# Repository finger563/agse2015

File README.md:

View this project on [CADLAB.io](https://cadlab.io/node/972). 

agse2015
========

This repository contains the design and implementation for the AGSE subsystem for the VAC 2015 year.

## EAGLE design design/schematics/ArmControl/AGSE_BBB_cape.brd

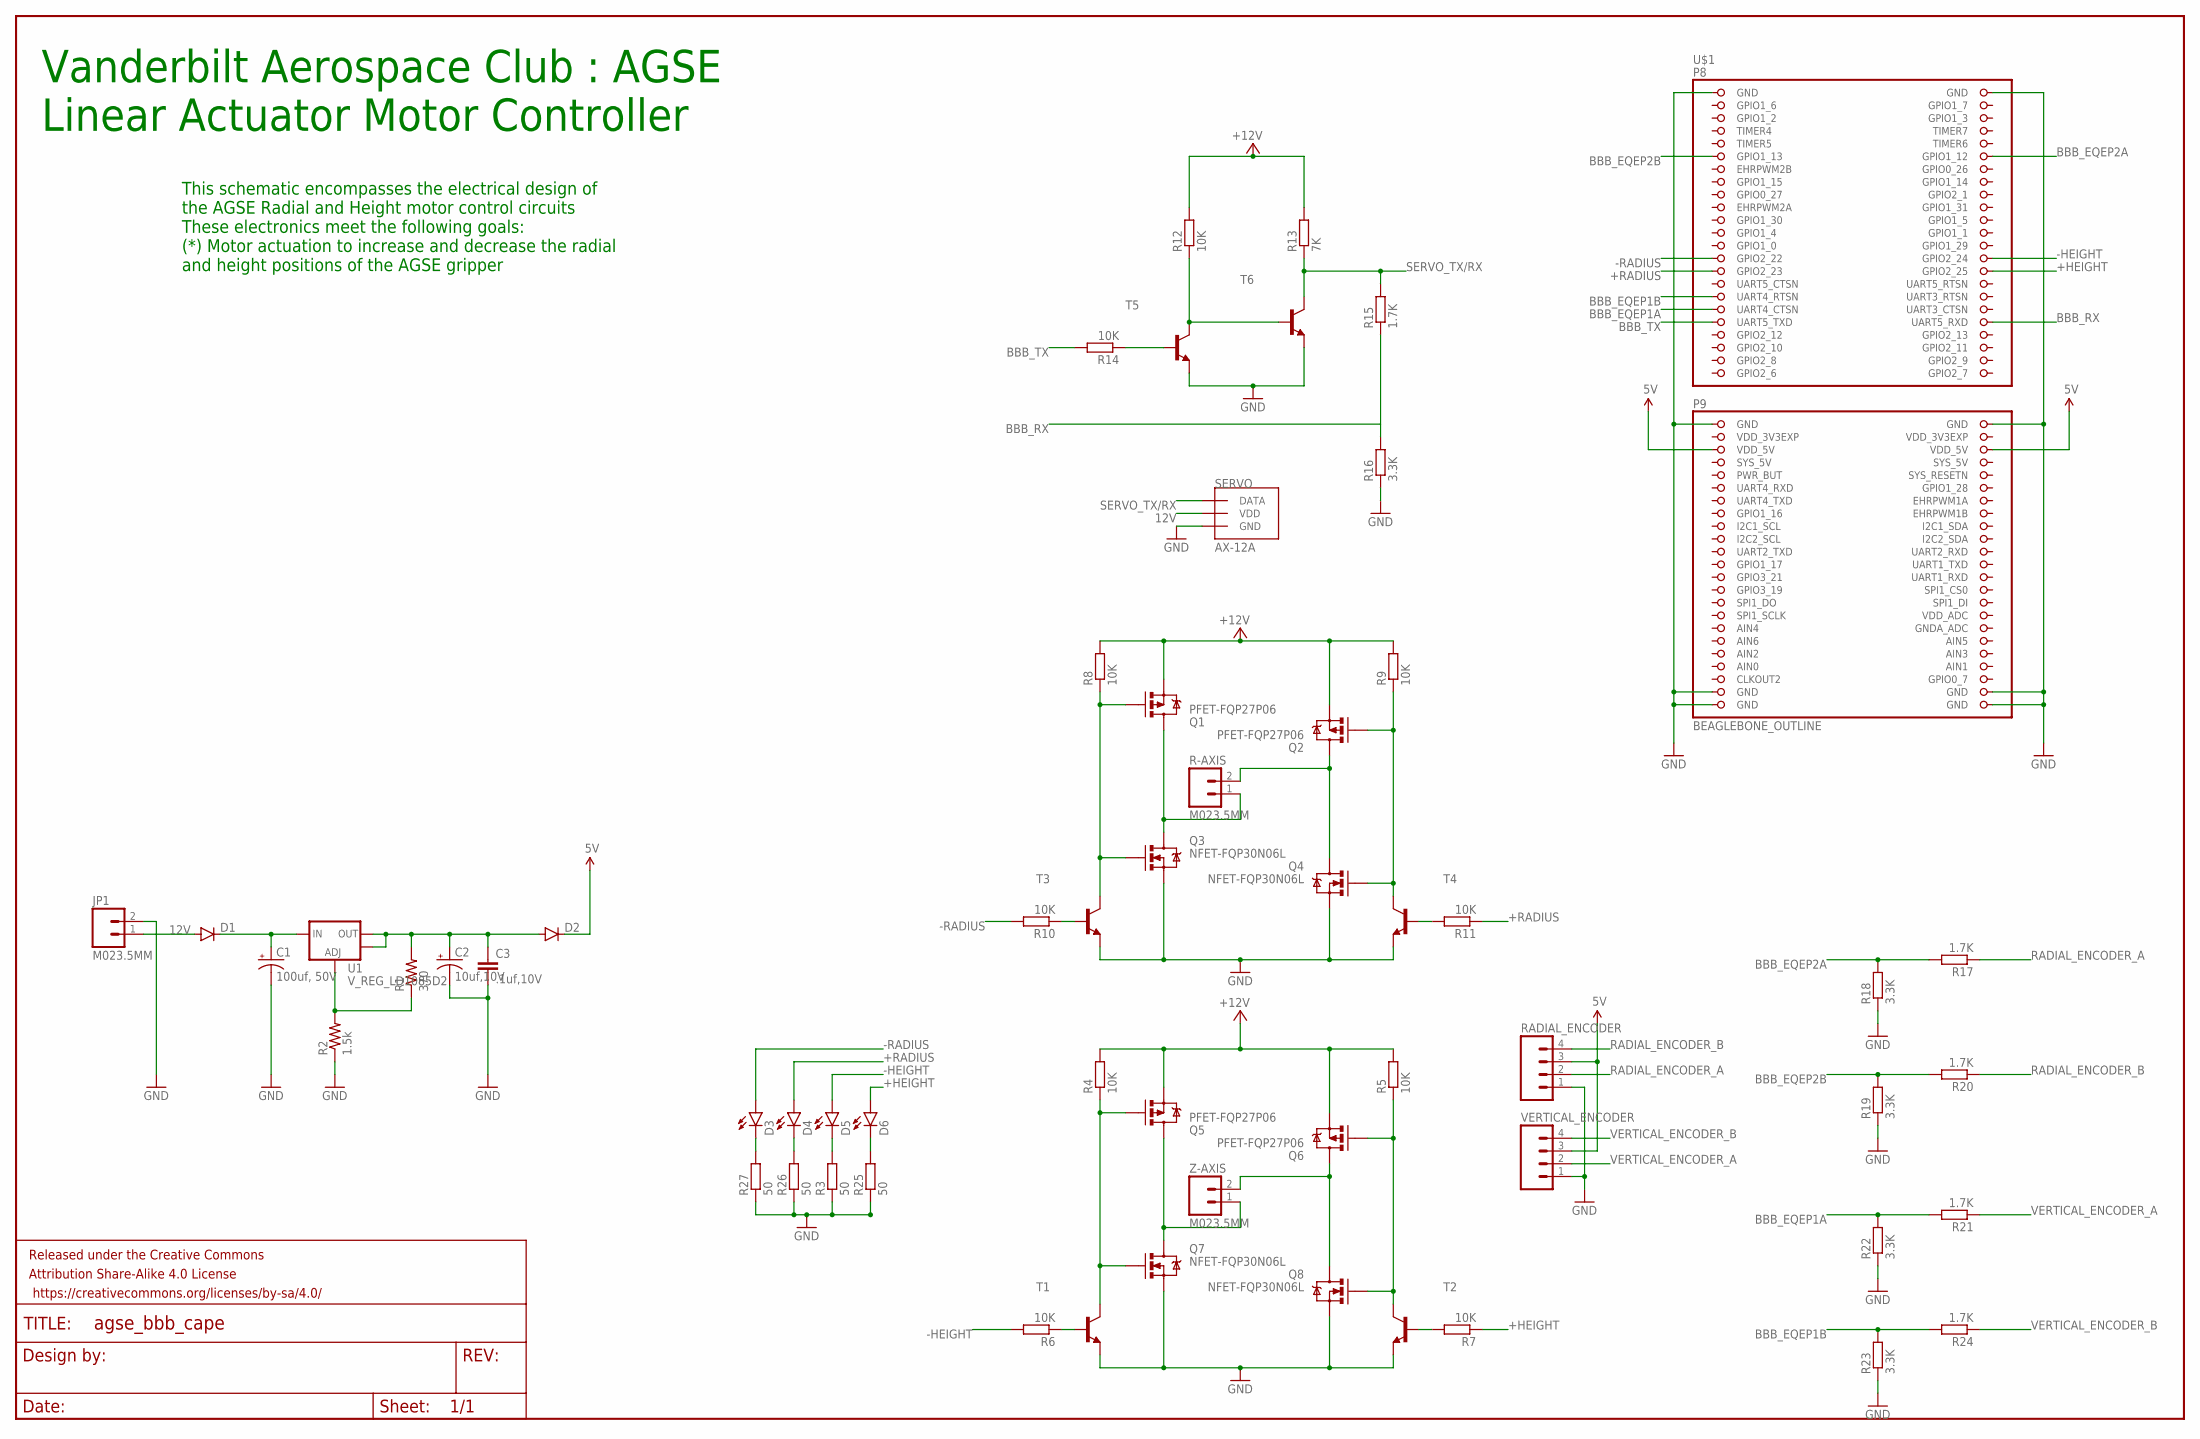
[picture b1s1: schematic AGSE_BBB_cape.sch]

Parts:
C1: 100uf, 50V; PANASONIC_D
C2: 10uf,10V; EIA3216
C3: .1uf,10V; 0402-CAP
D1: DIODESMA; SMA-DIODE
D2: DIODE1N4148; DIODE-1N4148
D3, D4, D5, D6: LED-FKIT-1206; FKIT-LED-1206
FRAME1: FRAME-LEDGER; CREATIVE_COMMONS
JP1: M023.5MM; SCREWTERMINAL-3.5MM-2
Q1, Q2, Q5, Q6: PFET-FQP27P06; TO220V
Q3, Q4, Q7, Q8: NFET-FQP30N06L; TO220V
R1: 370; 0402-RES
R2: 1.5k; 0402-RES
R3, R25, R26, R27: 50; M0805
R4, R5, R6, R7, R8, R9, R10, R11, R12, R14: 10K; M0805
R13: 7K; M0805
R15, R17, R20, R21, R24: 1.7K; M0805
R16, R18, R19, R22, R23: 3.3K; M0805
R-AXIS: M023.5MM; SCREWTERMINAL-3.5MM-2
RADIAL_ENCODER: M04POLAR; MOLEX-1X4
SERVO: AX-12A; SPOX-3
T1, T2, T3, T4, T5, T6: BF820-NPN-SOT23-BEC; SOT23-BEC
U1: V_REG_LD1085D2; D2PACK/A
U$1: BEAGLEBONE_OUTLINE; BEAGLEBONE_SHIELD
VERTICAL_ENCODER: M04POLAR; MOLEX-1X4
Z-AXIS: M023.5MM; SCREWTERMINAL-3.5MM-2

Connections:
5V: D2.C, RADIAL_ENCODER.3, U$1.51 (VDD_5V), U$1.52 (VDD_5V), VERTICAL_ENCODER.3
12V: D1.A, JP1.1, Q1.3 (S), Q2.3 (S), Q5.3 (S), Q6.3 (S), R4.2, R5.2, R8.2, R9.2, R12.2, R13.2, SERVO.P$2 (VDD)
+HEIGHT: D6.A, R7.1, U$1.30 (GPIO2_25)
+RADIUS: D4.A, R11.1, U$1.29 (GPIO2_23)
-HEIGHT: D5.A, R6.2, U$1.28 (GPIO2_24)
-RADIUS: D3.A, R10.2, U$1.27 (GPIO2_22)
AIN0: U$1.85 (AIN0)
BBB_EQEP1A: R21.2, R22.2, U$1.35 (UART4_CTSN)
BBB_EQEP1B: R23.2, R24.2, U$1.33 (UART4_RTSN)
BBB_EQEP2A: R17.2, R18.2, U$1.12 (GPIO1_12)
BBB_EQEP2B: R19.2, R20.2, U$1.11 (GPIO1_13)
BBB_RX: R15.1, R16.2, U$1.38 (UART5_RXD)
BBB_TX: R14.2, U$1.37 (UART5_TXD)
GND: C1.-, C2.C (-), C3.2, JP1.2, Q3.3 (S), Q4.3 (S), Q7.3 (S), Q8.3 (S), R2.1, R3.1, R16.1, R18.1, R19.1, R22.1, R23.1, R25.1, R26.1, R27.1, RADIAL_ENCODER.1, SERVO.P$3 (GND), T1.E, T2.E, T3.E, T4.E, T5.E, T6.E, U$1.1 (GND), U$1.2 (GND), U$1.47 (GND), U$1.48 (GND), U$1.89 (GND), U$1.90 (GND), U$1.91 (GND), U$1.92 (GND), VERTICAL_ENCODER.1
unnamed: D3.C, R27.2
unnamed: D4.C, R26.2
unnamed: C1.+, D1.C, U1.3 (IN)
unnamed: R1.1, R2.2, U1.1 (ADJ)
unnamed: D5.C, R3.2
unnamed: D6.C, R25.2
unnamed: Q5.1 (G), Q7.1 (G), R4.1, T1.C
unnamed: Q6.1 (G), Q8.1 (G), R5.1, T2.C
unnamed: R6.1, T1.B
unnamed: R7.2, T2.B
unnamed: Q1.1 (G), Q3.1 (G), R8.1, T3.C
unnamed: Q2.1 (G), Q4.1 (G), R9.1, T4.C
unnamed: R10.1, T3.B
unnamed: R11.2, T4.B
unnamed: R14.1, T5.B
unnamed: R12.1, T5.C, T6.B
R+: Q1.2 (D), Q3.2 (D), R-AXIS.1
R-: Q2.2 (D), Q4.2 (D), R-AXIS.2
RADIAL_ENCODER_A: R17.1, RADIAL_ENCODER.2
RADIAL_ENCODER_B: R20.1, RADIAL_ENCODER.4
SERVO_TX/RX: R13.1, R15.2, SERVO.P$1 (DATA), T6.C
SYS_5V: U$1.53 (SYS_5V)
VDD_3V3EXP: U$1.49 (VDD_3V3EXP), U$1.50 (VDD_3V3EXP)
VERTICAL_ENCODER_A: R21.1, VERTICAL_ENCODER.2
VERTICAL_ENCODER_B: R24.1, VERTICAL_ENCODER.4
VOUT: C2.A (+), C3.1, D2.A, R1.2, U1.2 (OUT), U1.TAB (OUT)
Z+: Q5.2 (D), Q7.2 (D), Z-AXIS.1
Z-: Q6.2 (D), Q8.2 (D), Z-AXIS.2

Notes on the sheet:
Vanderbilt Aerospace Club : AGSE Linear Actuator Motor Controller
This schematic encompasses the electrical design of the AGSE Radial and Height motor control circuits These electronics meet the following goals: (*) Motor actuation to increase and decrease the radial and height positions of the AGSE gripper

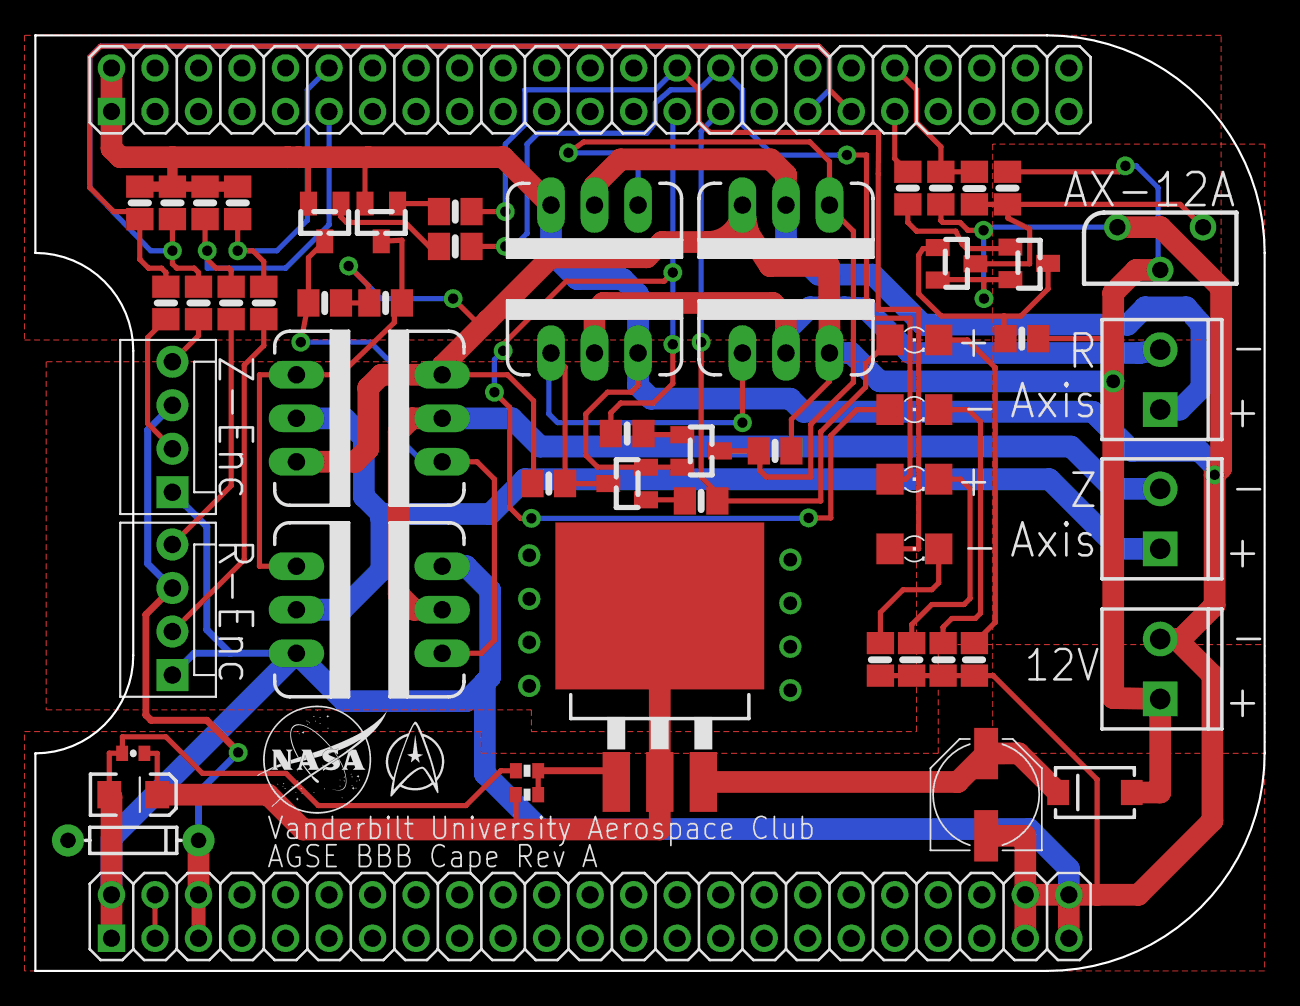
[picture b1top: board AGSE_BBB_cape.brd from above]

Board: 2 copper layers, 71.8 x 54.6 mm, 60 parts (0 on the bottom side), 40 nets.

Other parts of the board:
DRILEGEND: DRILEGEND

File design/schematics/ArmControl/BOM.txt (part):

Partlist exported from C:/Users/Pranav/Downloads/agse2015/design/schematics/ArmControl/AGSE_BBB_cape.sch at 2/26/2015 3:21:17 PM

Part             Value              Device                   Package               Description                                               MANEX        PROD_ID    
C1               100uf, 50V         CAP_POLD                 PANASONIC_D           Capacitor Polarized                                       123-0004264             
C2               10uf,10V           CAP_POL1206              EIA3216               Capacitor Polarized                                       123-0001192             
C3               .1uf,10V           CAP0402-CAP              0402-CAP              Capacitor                                                 123-0001047             
D1                                  DIODESMA                 SMA-DIODE             Diode                                                     130-0001388             
D2                                  DIODE1N4148              DIODE-1N4148          Diode                                                     130-0002546             
D3                                  LED-FKIT-1206            FKIT-LED-1206         LEDs                                                                              
D4                                  LED-FKIT-1206            FKIT-LED-1206         LEDs                                                                              
D5                                  LED-FKIT-1206            FKIT-LED-1206         LEDs                                                                              
D6                                  LED-FKIT-1206            FKIT-LED-1206         LEDs                                                                              
FRAME1           FRAME-LEDGER       FRAME-LEDGER             CREATIVE_COMMONS      Schematic Frame                                                                   
JP1              M023.5MM           M023.5MM                 SCREWTERMINAL-3.5MM-2 Standard 2-pin 0.1" header. Use with                      257-0004040  CONN-08399 
Q1               PFET-FQP27P06      MOSFET-PCHANNELFQP27P06  TO220V                Generic PMOSFET                                                                   
Q2               PFET-FQP27P06      MOSFET-PCHANNELFQP27P06  TO220V                Generic PMOSFET                                                                   
Q3               NFET-FQP30N06L     MOSFET-NCHANNELFQP30N06L TO220V                Common NMOSFET Parts                                                   TRANS-10060
Q4               NFET-FQP30N06L     MOSFET-NCHANNELFQP30N06L TO220V                Common NMOSFET Parts                                                   TRANS-10060
Q5               PFET-FQP27P06      MOSFET-PCHANNELFQP27P06  TO220V                Generic PMOSFET                                                                   
Q6               PFET-FQP27P06      MOSFET-PCHANNELFQP27P06  TO220V                Generic PMOSFET                                                                   
Q7               NFET-FQP30N06L     MOSFET-NCHANNELFQP30N06L TO220V                Common NMOSFET Parts                                                   TRANS-10060
Q8               NFET-FQP30N06L     MOSFET-NCHANNELFQP30N06L TO220V                Common NMOSFET Parts                                                   TRANS-10060
R-AXIS           M023.5MM           M023.5MM                 SCREWTERMINAL-3.5MM-2 Standard 2-pin 0.1" header. Use with                      257-0004040  CONN-08399 
R1               370                RESISTOR0402-RES         0402-RES              Resistor                                                  110-0003316             
R2               1.5k               RESISTOR0402-RES         0402-RES              Resistor                                                  110-0001936             
R3               50                 R-EU_M0805               M0805                 RESISTOR, European symbol                                                         
R4               10K                R-EU_M0805               M0805                 RESISTOR, European symbol                                                         
R5               10K                R-EU_M0805               M0805                 RESISTOR, European symbol                                                         
R6               10K                R-EU_M0805               M0805                 RESISTOR, European symbol                                                         
R7               10K                R-EU_M0805               M0805                 RESISTOR, European symbol                                                         
R8               10K                R-EU_M0805               M0805                 RESISTOR, European symbol                                                         
R9               10K                R-EU_M0805               M0805                 RESISTOR, European symbol                                                         
R10              10K                R-EU_M0805               M0805                 RESISTOR, European symbol                                                         
R11              10K                R-EU_M0805               M0805                 RESISTOR, European symbol                                                         
R12              10K                R-EU_M0805               M0805                 RESISTOR, European symbol                                                         
R13              7K                 R-EU_M0805               M0805                 RESISTOR, European symbol                                                         
R14              10K                R-EU_M0805               M0805                 RESISTOR, European symbol                                                         
R15              1.7K               R-EU_M0805               M0805                 RESISTOR, European symbol                                                         
R16              3.3K               R-EU_M0805               M0805                 RESISTOR, European symbol                                                         
R17              1.7K               R-EU_M0805               M0805                 RESISTOR, European symbol                                                         
R18              3.3K               R-EU_M0805               M0805                 RESISTOR, European symbol                                                         
R19              3.3K               R-EU_M0805               M0805                 RESISTOR, European symbol                                                         
R20              1.7K               R-EU_M0805               M0805                 RESISTOR, European symbol                                                         
R21              1.7K               R-EU_M0805               M0805                 RESISTOR, European symbol                                                         
R22              3.3K               R-EU_M0805               M0805                 RESISTOR, European symbol                                                         
R23              3.3K               R-EU_M0805               M0805                 RESISTOR, European symbol                                                         
R24              1.7K               R-EU_M0805               M0805                 RESISTOR, European symbol                                                         
R25              50                 R-EU_M0805               M0805                 RESISTOR, European symbol                                                         
R26              50                 R-EU_M0805               M0805                 RESISTOR, European symbol                                                         
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
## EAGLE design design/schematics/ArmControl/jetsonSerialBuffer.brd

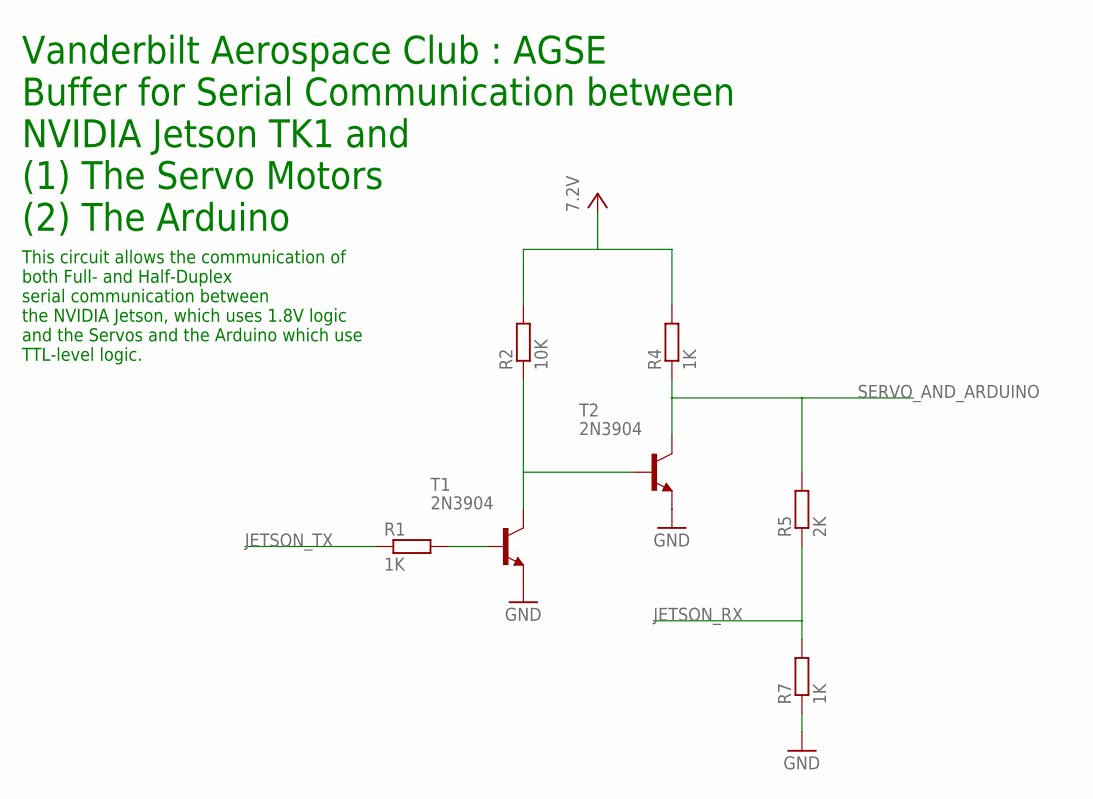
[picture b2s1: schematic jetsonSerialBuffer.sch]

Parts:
R1, R4, R7: 1K; 0309/10
R2: 10K; 0309/10
R5: 2K; 0309/10
T1, T2: 2N3904; TO92

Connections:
GND: R7.1, T1.3 (E), T2.3 (E)
JETSON_RX: R5.1, R7.2
JETSON_TX: R1.1
unnamed: R1.2, T1.2 (B)
unnamed: R2.1, T1.1 (C), T2.2 (B)
SERVO_AND_ARDUINO: R4.1, R5.2, T2.1 (C)
VCC: R2.2, R4.2

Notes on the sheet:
Vanderbilt Aerospace Club : AGSE Buffer for Serial Communication between NVIDIA Jetson TK1 and (1) The Servo Motors (2) The Arduino
This circuit allows the communication of both Full- and Half-Duplex serial communication between the NVIDIA Jetson, which uses 1.8V logic and the Servos and the Arduino which use TTL-level logic.

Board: 2 copper layers, 7 parts (0 on the bottom side), 6 nets, no tracks yet.

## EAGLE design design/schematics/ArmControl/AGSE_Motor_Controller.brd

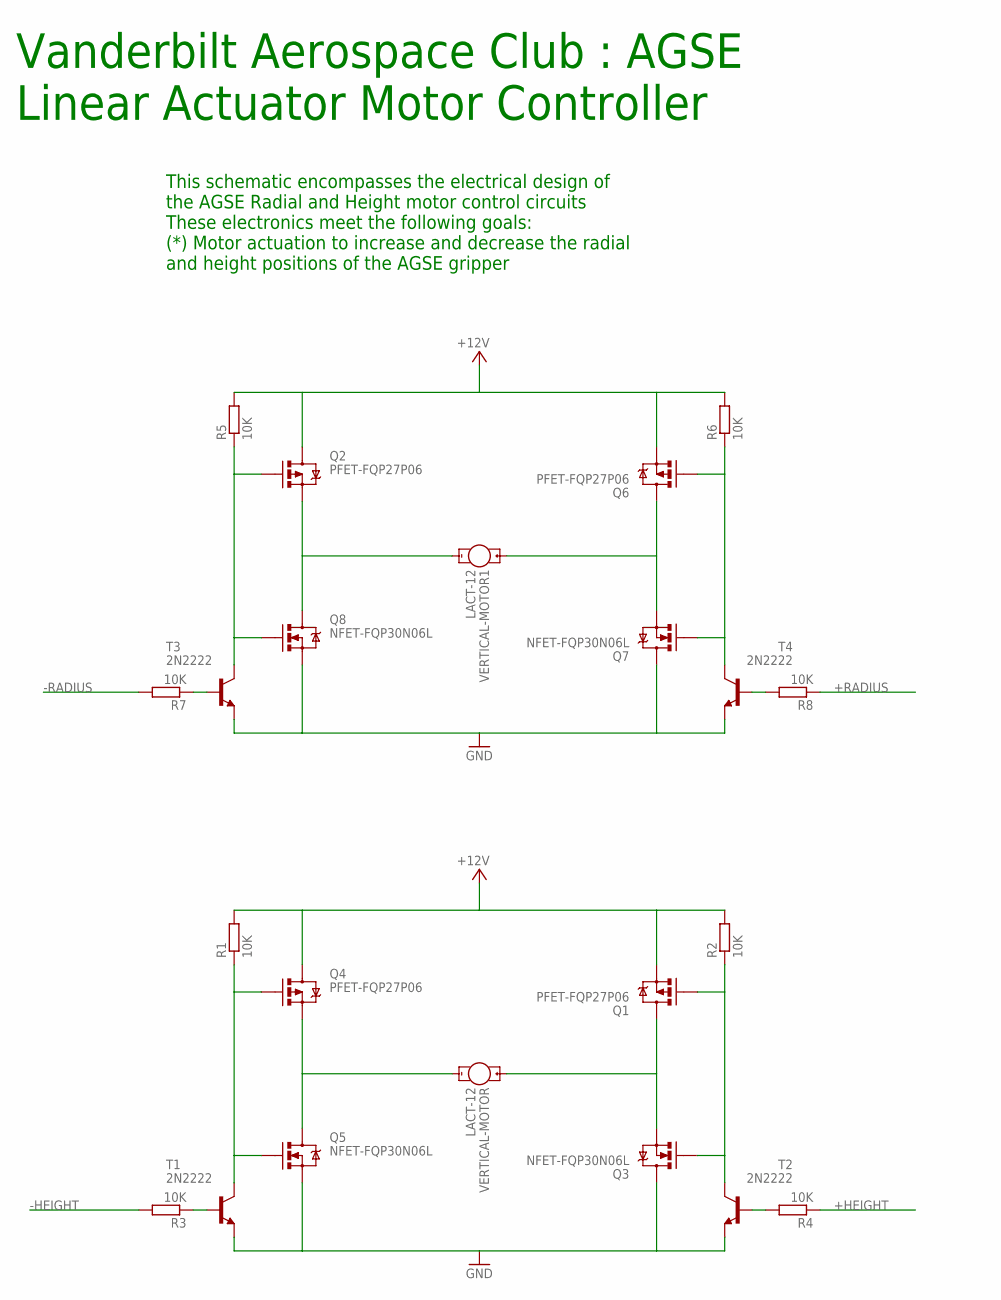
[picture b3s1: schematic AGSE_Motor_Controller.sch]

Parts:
Q1, Q2, Q4, Q6: PFET-FQP27P06; TO220V
Q3, Q5, Q7, Q8: NFET-FQP30N06L; TO220V
R1, R2, R3, R4, R5, R6, R7, R8: 10K; 0207/12
T1, T2, T3, T4: 2N2222; TO18
VERTICAL-MOTOR, VERTICAL-MOTOR1: LACT-12; VIBE-MOTOR-10MM

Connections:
+5V: Q1.3 (S), Q2.2 (D), Q4.2 (D), Q6.3 (S), R1.2, R2.2, R5.2, R6.2
+HEIGHT: R4.1
+RADIUS: R8.1
-HEIGHT: R3.2
-RADIUS: R7.2
GND: Q3.2 (D), Q5.3 (S), Q7.2 (D), Q8.3 (S), T1.1 (E), T2.1 (E), T3.1 (E), T4.1 (E)
unnamed: Q4.3 (S), Q5.2 (D), VERTICAL-MOTOR.-
unnamed: Q1.2 (D), Q3.3 (S), VERTICAL-MOTOR.+
unnamed: Q4.1 (G), Q5.1 (G), R1.1, T1.3 (C)
unnamed: Q1.1 (G), Q3.1 (G), R2.1, T2.3 (C)
unnamed: R3.1, T1.2 (B)
unnamed: R4.2, T2.2 (B)
unnamed: Q6.2 (D), Q7.3 (S), VERTICAL-MOTOR1.+
unnamed: Q2.3 (S), Q8.2 (D), VERTICAL-MOTOR1.-
unnamed: Q2.1 (G), Q8.1 (G), R5.1, T3.3 (C)
unnamed: Q6.1 (G), Q7.1 (G), R6.1, T4.3 (C)
unnamed: R7.1, T3.2 (B)
unnamed: R8.2, T4.2 (B)

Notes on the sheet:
Vanderbilt Aerospace Club : AGSE Linear Actuator Motor Controller
This schematic encompasses the electrical design of the AGSE Radial and Height motor control circuits These electronics meet the following goals: (*) Motor actuation to increase and decrease the radial and height positions of the AGSE gripper

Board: 2 copper layers, 22 parts (0 on the bottom side), 14 nets, no tracks yet.

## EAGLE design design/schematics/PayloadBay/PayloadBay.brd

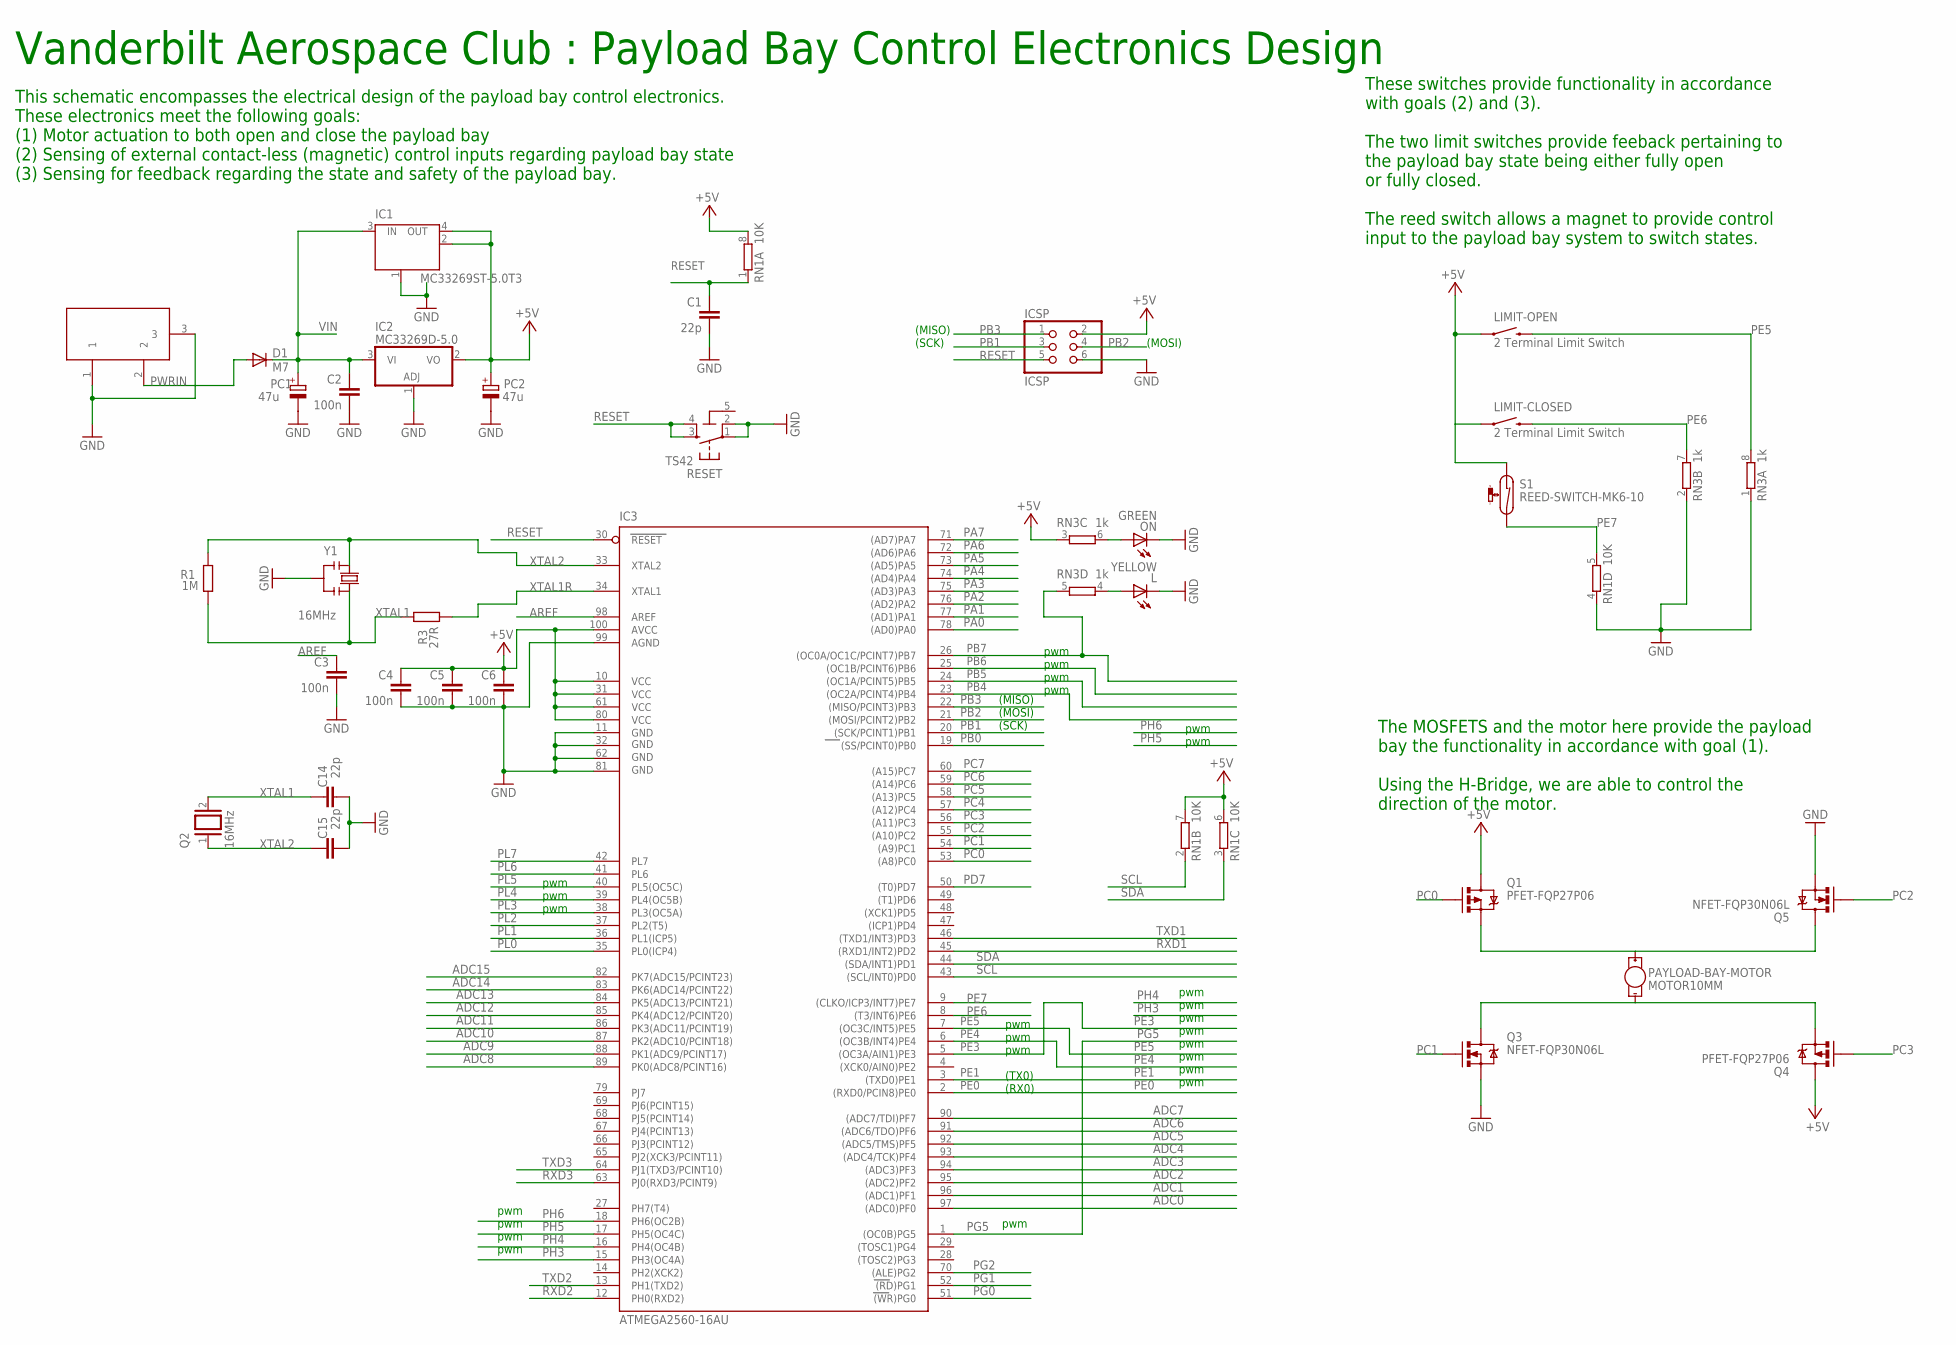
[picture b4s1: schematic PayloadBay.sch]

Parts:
C1, C14, C15: 22p; C0603-ROUND
C2, C3, C4, C5, C6: 100n; C0603-ROUND
D1: M7; SMB
IC1: MC33269ST-5.0T3; SOT223
IC2: MC33269D-5.0; DPACK
IC3: ATMEGA2560-16AU; TQFP100
ICSP: ICSP; 2X03
L: YELLOW; CHIP-LED0805
LIMIT-CLOSED: 2 Terminal Limit Switch; TACTILE-PTH-12MM
LIMIT-OPEN: 2 Terminal Limit Switch; TACTILE-PTH-12MM
ON: GREEN; CHIP-LED0805
PAYLOAD-BAY-MOTOR: MOTOR10MM; VIBE-MOTOR-10MM
PC1, PC2: 47u; PANASONIC_D
Q1, Q4: PFET-FQP27P06; TO220V
Q2: 16MHz; QS
Q3, Q5: NFET-FQP30N06L; TO220V
R1: 1M; R0603-ROUND
R3: 27R; R0603-ROUND
RESET: TS42
RN1: 10K; CAT16
RN3: 1k; CAY16
S1: REED-SWITCH-MK6-10; MK6-10
X1: DC21MMX; DC-21MM
Y1: 16MHz; RESONATOR

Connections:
5-GND: RESET.5 (5-GND)
+5V: C4.1, C5.1, C6.1, IC1.2 (OUT), IC1.4 (OUT), IC2.2 (VO), IC3.10 (VCC), IC3.31 (VCC1), IC3.61 (VCC2), IC3.80 (VCC3), IC3.100 (AVCC), ICSP.2, LIMIT-CLOSED.1, LIMIT-OPEN.1, PC2.+, Q1.2 (D), Q4.2 (D), RN1.6 (2), RN1.7 (2), RN1.8 (2), RN3.3 (1), S1.1
ADC0: IC3.97 ((ADC0)PF0)
ADC1: IC3.96 ((ADC1)PF1)
ADC2: IC3.95 ((ADC2)PF2)
ADC3: IC3.94 ((ADC3)PF3)
ADC4: IC3.93 ((ADC4/TCK)PF4)
ADC5: IC3.92 ((ADC5/TMS)PF5)
ADC6: IC3.91 ((ADC6/TDO)PF6)
ADC7: IC3.90 ((ADC7/TDI)PF7)
ADC8: IC3.89 (PK0(ADC8/PCINT16))
ADC9: IC3.88 (PK1(ADC9/PCINT17))
ADC10: IC3.87 (PK2(ADC10/PCINT18))
ADC11: IC3.86 (PK3(ADC11/PCINT19))
ADC12: IC3.85 (PK4(ADC12/PCINT20))
ADC13: IC3.84 (PK5(ADC13/PCINT21))
ADC14: IC3.83 (PK6(ADC14/PCINT22))
ADC15: IC3.82 (PK7(ADC15/PCINT23))
AREF: C3.1, IC3.98 (AREF)
GND: C1.2, C2.2, C3.2, C4.2, C5.2, C6.2, C14.1, C15.1, IC1.1 (GND/ADJ), IC2.1 (ADJ), IC3.11 (GND), IC3.32 (GND1), IC3.62 (GND2), IC3.81 (GND3), IC3.99 (AGND), ICSP.6, L.C, ON.C, PC1.-, PC2.-, Q3.3 (S), Q5.3 (S), RESET.1, RESET.2, RN1.4 (1), RN3.1, RN3.2 (1), X1.1, X1.3, Y1.2
unnamed: PAYLOAD-BAY-MOTOR.+, Q1.3 (S), Q5.2 (D)
unnamed: L.A, RN3.4 (1)
unnamed: ON.A, RN3.6 (2)
unnamed: PAYLOAD-BAY-MOTOR.-, Q3.2 (D), Q4.3 (S)
PA0: IC3.78 ((AD0)PA0)
PA1: IC3.77 ((AD1)PA1)
PA2: IC3.76 ((AD2)PA2)
PA3: IC3.75 ((AD3)PA3)
PA4: IC3.74 ((AD4)PA4)
PA5: IC3.73 ((AD5)PA5)
PA6: IC3.72 ((AD6)PA6)
PA7: IC3.71 ((AD7)PA7)
PB0: IC3.19 ((SS/PCINT0)PB0)
PB1: IC3.20 ((SCK/PCINT1)PB1), ICSP.3
PB2: IC3.21 ((MOSI/PCINT2)PB2), ICSP.4
PB3: IC3.22 ((MISO/PCINT3)PB3), ICSP.1
PB4: IC3.23 ((OC2A/PCINT4)PB4)
PB5: IC3.24 ((OC1A/PCINT5)PB5)
PB6: IC3.25 ((OC1B/PCINT6)PB6)
PB7: IC3.26 ((OC0A/OC1C/PCINT7)PB7), RN3.5 (2)
PC0: IC3.53 ((A8)PC0)
PC1: IC3.54 ((A9)PC1), Q3.1 (G)
PC2: IC3.55 ((A10)PC2), Q5.1 (G)
PC3: IC3.56 ((A11)PC3), Q4.1 (G)
PC4: IC3.57 ((A12)PC4)
PC5: IC3.58 ((A13)PC5)
PC6: IC3.59 ((A14)PC6)
PC7: IC3.60 ((A15)PC7)
PD7: IC3.50 ((T0)PD7)
PE0: IC3.2 ((RXD0/PCIN8)PE0)
PE1: IC3.3 ((TXD0)PE1)
PE3: IC3.5 ((OC3A/AIN1)PE3)
PE4: IC3.6 ((OC3B/INT4)PE4)
PE5: IC3.7 ((OC3C/INT5)PE5), LIMIT-OPEN.3 (2), RN3.8 (2)
PE6: IC3.8 ((T3/INT6)PE6), LIMIT-CLOSED.3 (2), RN3.7 (2)
PE7: IC3.9 ((CLKO/ICP3/INT7)PE7), RN1.5 (2), S1.2
PG0: IC3.51 ((WR)PG0)
PG1: IC3.52 ((RD)PG1)
PG2: IC3.70 ((ALE)PG2)
PG5: IC3.1 ((OC0B)PG5)
PH3: IC3.15 (PH3(OC4A))
PH4: IC3.16 (PH4(OC4B))
PH5: IC3.17 (PH5(OC4C))
PH6: IC3.18 (PH6(OC2B))
PL0: IC3.35 (PL0(ICP4))
PL1: IC3.36 (PL1(ICP5))
PL2: IC3.37 (PL2(T5))
PL3: IC3.38 (PL3(OC5A))
PL4: IC3.39 (PL4(OC5B))
PL5: IC3.40 (PL5(OC5C))
PL6: IC3.41 (PL6)
PL7: IC3.42 (PL7)
PWRIN: D1.A, X1.2
RESET: C1.1, IC3.30 (RESET), ICSP.5, RESET.3, RESET.4, RN1.1
RXD1: IC3.45 ((RXD1/INT2)PD2)
RXD2: IC3.12 (PH0(RXD2))
RXD3: IC3.63 (PJ0(RXD3/PCINT9))
SCL: IC3.43 ((SCL/INT0)PD0), RN1.2 (1)
SDA: IC3.44 ((SDA/INT1)PD1), RN1.3 (1)
TXD1: IC3.46 ((TXD1/INT3)PD3)
TXD2: IC3.13 (PH1(TXD2))
TXD3: IC3.64 (PJ1(TXD3/PCINT10))
VIN: C2.1, D1.C, IC1.3 (IN), IC2.3 (VI), PC1.+
XTAL1: C14.2, Q2.2, R1.1, R3.2, Y1.3
XTAL1R: IC3.34 (XTAL1), R3.1
XTAL2: C15.2, IC3.33 (XTAL2), Q2.1, R1.2, Y1.1

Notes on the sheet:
(SCK)
(MISO)
(MOSI)
pwm
(TX0)
(RX0)
Vanderbilt Aerospace Club : Payload Bay Control Electronics Design
This schematic encompasses the electrical design of the payload bay control electronics. These electronics meet the following goals: (1) Motor actuation to both open and close the payload bay (2) Sensing of external contact-less (magnetic) control inputs regarding payload bay state (3) Sensing for 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
These switches provide functionality in accordance with goals (2) and (3). The two limit switches provide feeback pertaining to the payload bay state being either fully open or fully closed. The reed switch allows a magnet to provide control input to the payload bay system to switch states.
The MOSFETS and the motor here provide the payload bay the functionality in accordance with goal (1). Using the H-Bridge, we are able to control the direction of the motor.

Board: 2 copper layers, 33 parts (0 on the bottom side), 25 nets, no tracks yet.

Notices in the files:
parts and their libraries:
SparkFun-PowerIC: Licensing: CC v3.0 Share-Alike You are welcome to use this library for commercial purposes.
SparkFun-Aesthetics: Released under the Creative Commons Attribution Share-Alike 4.0 License
SparkFun-Aesthetics: https://creativecommons.org/licenses/by-sa/4.0
